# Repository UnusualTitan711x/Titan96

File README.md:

# Titan96  

**Titan96** is a compact 96% low-profile mechanical keyboard designed with sleek aesthetic. Powered by **KMK firmware** and built around the **Orpheus Pico microcontroller** by Hack Club.  

## Features  
- **96% Layout** – Compact yet functional, with all essential keys in a dense layout.  
- **Low-Profile Design** – Slimmer keys and case for a modern, ergonomic feel.  
- **KMK Firmware** – Highly customizable keymaps and macros using CircuitPython.  
- **Orpheus Pico MCU** – A powerful and open-source microcontroller by Hack Club.  
- **100 Keys** – Full numpad and navigation keys.  

## Parts
### CAD

### Schematic

### PCB

## Firmware & Software  
The Titan96 runs on **KMK**, a Python-based keyboard firmware for CircuitPython-compatible microcontrollers.  

### Setup Instructions  
1. **Flash CircuitPython** onto the Orpheus Pico.  
2. **Install KMK firmware** by copying the KMK files to the microcontroller.  
3. **Configure keymap** by editing `code.py` to match your layout.  
4. **Customize macros, layers, and RGB** (if supported) via KMK.  

For detailed KMK setup, refer to the [official KMK documentation](https://github.com/KMKfw/kmk_firmware).  

## Bill of Materials (BOM)  
| Part | Quantity | Price | Link | Notes |  
|------|----------|-------|------|-------|  
| Orpheus Pico MCU | 1 | N/A | N/A | Microcontroller by Hack Club |  
| Low-profile mechanical switches | 100 | $40.07 | [AliExpress](https://www.aliexpress.com/item/1005004620638633.html?spm=a2g0o.cart.0.0.422438daRMYwqx&mp=1&pdp_npi=5%40dis%21USD%21USD%2038.00%21USD%2034.20%21%21USD%2034.20%21%21%21%40211b65de17522704719968508eea63%2112000029862619758%21ct%21CM%216291529643%21%211%210) | Gateron Low-Profile |  
| Keycaps | 100 | $22.14 | [AliExpress](https://www.aliexpress.com/item/1005007074678857.html?spm=a2g0o.cart.0.0.422438daRMYwqx&mp=1&pdp_npi=5%40dis%21USD%21USD%2018.72%21USD%2014.98%21%21USD%2014.98%21%21%21%40211b65de17522704719968508eea63%2112000043563688519%21ct%21CM%216291529643%21%211%210) | MX stems |  
| PCB | 1 | N/A |  N/A | Custom Titan96 PCB |  
| Plate | 1 |  N/A | N/A |3D printed |  
| Case | 1 | N/A | N/A | 3D printed |  
| Diodes | 100 | $4.7 | [AliExpress](https://www.aliexpress.com/item/1005004333197874.html?spm=a2g0o.cart.0.0.422438daRMYwqx&mp=1&pdp_npi=5%40dis%21USD%21USD%200.33%21USD%200.31%21%21USD%200.31%21%21%21%40211b65de17522704719968508eea63%2112000028793174971%21ct%21CM%216291529643%21%211%210) | 1N4148 |  
| Stabilizers | 2u x 5, 6.5u x 1 | $15.58 | [AliExpress](https://www.aliexpress.com/item/1005005296240590.html?spm=a2g0o.cart.0.0.422438daRMYwqx&mp=1&pdp_npi=5%40dis%21USD%21USD%2011.59%21USD%2011.59%21%21USD%2011.59%21%21%21%40211b65de17522704719968508eea63%2112000032530884498%21ct%21CM%216291529643%21%211%210) | For larger keys (spacebar, Enter, etc.) |  
| OLED Screen 128 x 32 | 1 | $5.36 | [AliExpress](https://www.aliexpress.com/item/1005008670382155.html?spm=a2g0o.cart.0.0.422438daRMYwqx&mp=1&pdp_npi=5%40dis%21USD%21USD%201.63%21USD%201.14%21%21USD%201.14%21%21%21%40211b65de17522704719968508eea63%2112000046171658344%21ct%21CM%216291529643%21%211%210) | Screen |  
| M2 screws | 5 | $4.8 | [AliExpress](https://www.aliexpress.com/item/1005004533251852.html?spm=a2g0o.cart.0.0.286f38dacsLKbg&mp=1&pdp_npi=5%40dis%21USD%21USD%201.55%21USD%201.32%21%21USD%201.32%21%21%21%40211b618e17522580510792994e43dd%2112000029523312277%21ct%21CM%216291529643%21%211%210) | To screw the plate into the case |
| M2 threaded inserts | 5 | $5.87 | [AliExpress](https://www.aliexpress.com/item/1005003582355741.html?spm=a2g0o.cart.0.0.286f38dacsLKbg&mp=1&pdp_npi=5%40dis%21USD%21USD%201.69%21USD%200.52%21%21USD%200.52%21%21%21%40211b618e17522580510792994e43dd%2112000026370649721%21ct%21CM%216291529643%21%211%210) | To screw the plate into the case |
 
*NB: All these prices include shipping to Cameroon*

Total : $98.52
## License  
This project is open-source under the **MIT License**.  

## Extra Renders

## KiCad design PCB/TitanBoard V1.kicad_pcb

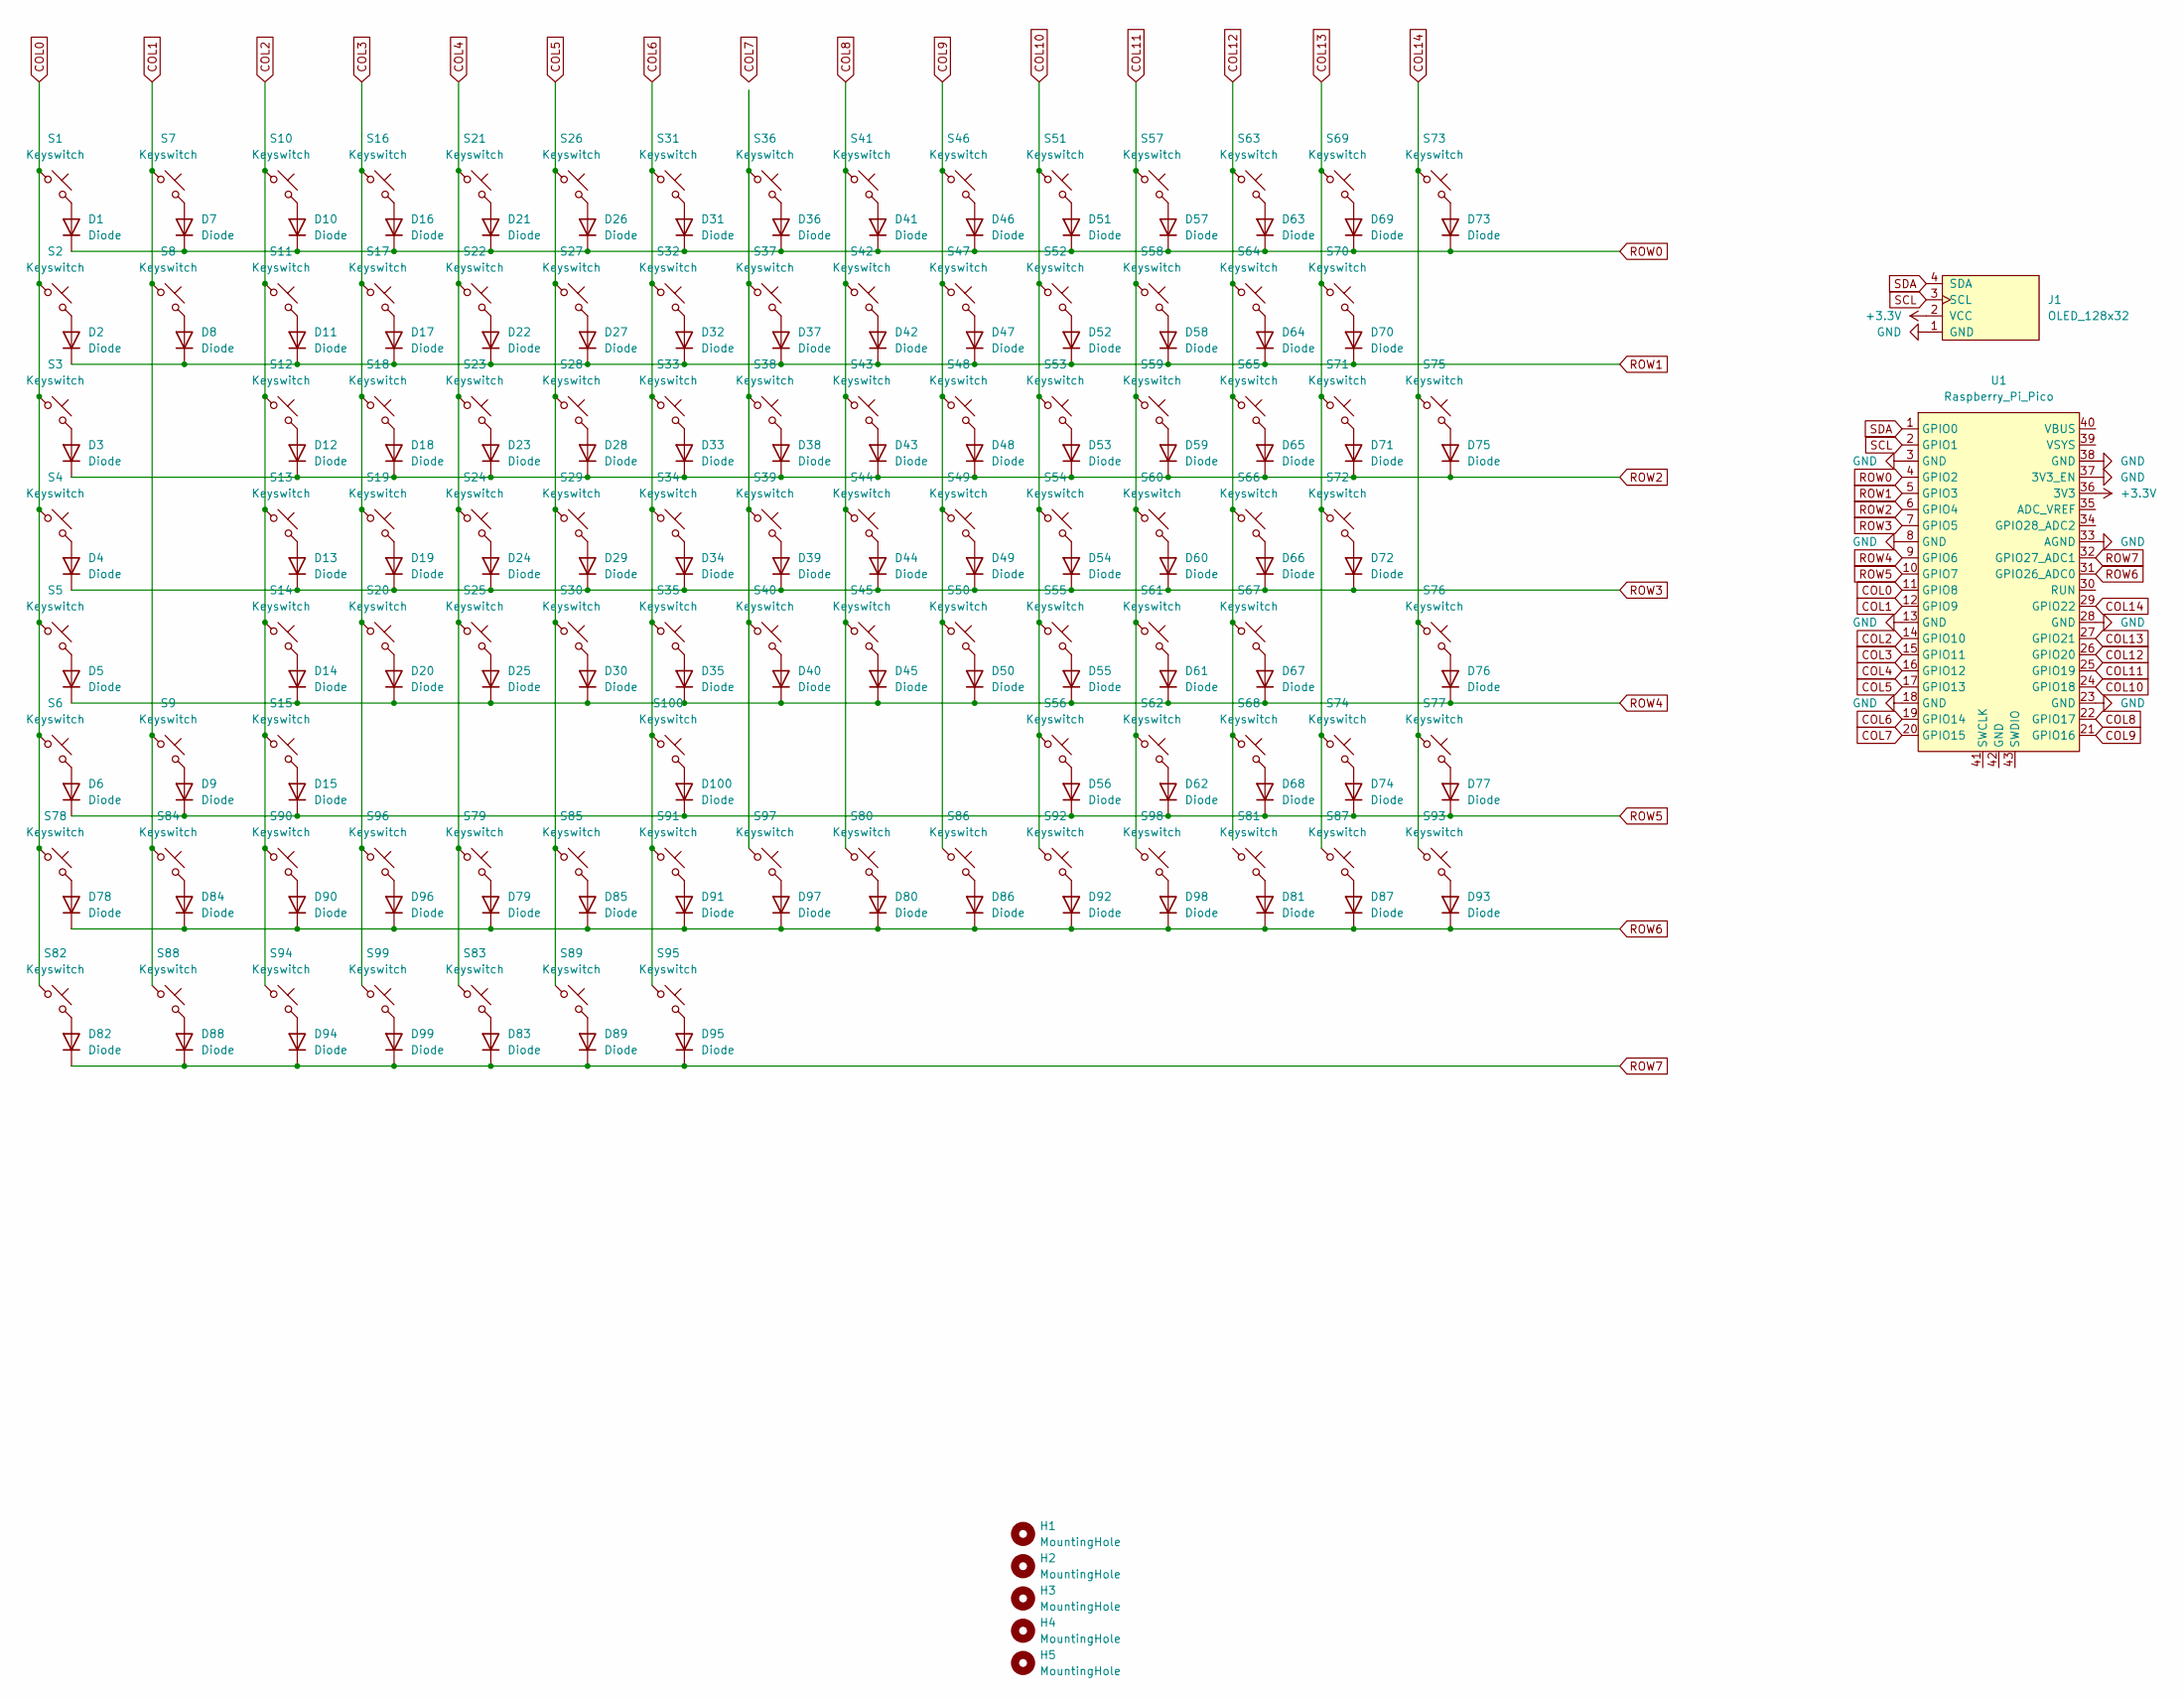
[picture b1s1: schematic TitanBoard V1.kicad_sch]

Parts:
D1, D2, D3, D4, D5, D6, D7, D8, D9, D10, D11, D12, D13, D14, D15, D16, D17, D18, D19, D20, D21, D22, D23, D24, D25, D26, D27, D28, D29, D30, D31, D32, D33, D34, D35, D36, D37, D38, D39, D40, D41, D42, D43, D44, D45, D46, D47, D48, D49, D50, D51, D52, D53, D54, D55, D56, D57, D58, D59, D60, D61, D62, D63, D64, D65, D66, D67, D68, D69, D70, D71, D72, D73, D74, D75, D76, D77, D78, D79, D80, D81, D82, D83, D84, D85, D86, D87, D88, D89, D90, D91, D92, D93, D94, D95, D96, D97, D98, D99, D100: Diode; Diode_DO-35
H1, H2, H3, H4, H5: MountingHole; MountingHole_2.2mm_M2
J1: OLED_128x32
S1, S2, S7, S8, S10, S11, S12, S13, S14, S16, S17, S18, S19, S20, S21, S22, S23, S24, S25, S26, S27, S28, S29, S30, S31, S32, S33, S34, S35, S36, S37, S38, S39, S40, S41, S42, S43, S44, S45, S46, S47, S48, S49, S50, S51, S52, S53, S54, S55, S56, S57, S58, S59, S60, S61, S62, S63, S64, S65, S66, S68, S69, S71, S73, S74, S76, S77, S78, S79, S80, S81, S82, S83, S84, S85, S86, S87, S88, S89, S90, S91, S92, S93, S94, S95, S96, S97: Keyswitch; Gateron-KS33-Solderable-1U
S3, S75: Keyswitch; Gateron-KS33-Solderable-1.5U
S4, S67: Keyswitch; Gateron-KS33-Solderable-1.75U
S5, S72: Keyswitch; Gateron-KS33-Solderable-2.25U
S6, S9, S15: Keyswitch; Gateron-KS33-Solderable-1.25U
S70, S98, S99: Keyswitch; Gateron-KS33-Solderable-2U
S100: Keyswitch; Gateron-KS33-Solderable-6.25U
U1: Raspberry_Pi_Pico

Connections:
+3.3V: J1.2 (VCC), U1.36 (3V3)
COL0: S1.1, S2.1, S3.1, S4.1, S5.1, S6.1, S78.1, S82.1, U1.11 (GPIO8)
COL1: S7.1, S8.1, S9.1, S84.1, S88.1, U1.12 (GPIO9)
COL2: S10.1, S11.1, S12.1, S13.1, S14.1, S15.1, S90.1, S94.1, U1.14 (GPIO10)
COL3: S16.1, S17.1, S18.1, S19.1, S20.1, S96.1, S99.1, U1.15 (GPIO11)
COL4: S21.1, S22.1, S23.1, S24.1, S25.1, S79.1, S83.1, U1.16 (GPIO12)
COL5: S26.1, S27.1, S28.1, S29.1, S30.1, S85.1, S89.1, U1.17 (GPIO13)
COL6: S31.1, S32.1, S33.1, S34.1, S35.1, S91.1, S95.1, S100.1, U1.19 (GPIO14)
COL7: U1.20 (GPIO15)
COL8: S41.1, S42.1, S43.1, S44.1, S45.1, S80.1, U1.22 (GPIO17)
COL9: S46.1, S47.1, S48.1, S49.1, S50.1, S86.1, U1.21 (GPIO16)
COL10: S51.1, S52.1, S53.1, S54.1, S55.1, S56.1, S92.1, U1.24 (GPIO18)
COL11: S57.1, S58.1, S59.1, S60.1, S61.1, S62.1, S98.1, U1.25 (GPIO19)
COL12: S63.1, S64.1, S65.1, S66.1, S67.1, S68.1, U1.26 (GPIO20)
COL13: S69.1, S70.1, S71.1, S72.1, S74.1, S87.1, U1.27 (GPIO21)
COL14: S73.1, S75.1, S76.1, S77.1, S93.1, U1.29 (GPIO22)
GND: J1.1 (GND), U1.3 (GND), U1.8 (GND), U1.13 (GND), U1.18 (GND), U1.23 (GND), U1.28 (GND), U1.33 (AGND), U1.37 (3V3_EN), U1.38 (GND)
unnamed: D1.2 (A), S1.2
unnamed: D2.2 (A), S2.2
unnamed: D3.2 (A), S3.2
unnamed: D4.2 (A), S4.2
unnamed: D5.2 (A), S5.2
unnamed: D6.2 (A), S6.2
unnamed: D7.2 (A), S7.2
unnamed: D8.2 (A), S8.2
unnamed: D9.2 (A), S9.2
unnamed: D10.2 (A), S10.2
unnamed: D11.2 (A), S11.2
unnamed: D12.2 (A), S12.2
unnamed: D13.2 (A), S13.2
unnamed: D14.2 (A), S14.2
unnamed: D15.2 (A), S15.2
unnamed: D16.2 (A), S16.2
unnamed: D17.2 (A), S17.2
unnamed: D18.2 (A), S18.2
unnamed: D19.2 (A), S19.2
unnamed: D20.2 (A), S20.2
unnamed: D21.2 (A), S21.2
unnamed: D22.2 (A), S22.2
unnamed: D23.2 (A), S23.2
unnamed: D24.2 (A), S24.2
unnamed: D25.2 (A), S25.2
unnamed: D26.2 (A), S26.2
unnamed: D27.2 (A), S27.2
unnamed: D28.2 (A), S28.2
unnamed: D29.2 (A), S29.2
unnamed: D30.2 (A), S30.2
unnamed: D31.2 (A), S31.2
unnamed: D32.2 (A), S32.2
unnamed: D33.2 (A), S33.2
unnamed: D34.2 (A), S34.2
unnamed: D35.2 (A), S35.2
unnamed: D36.2 (A), S36.2
unnamed: D37.2 (A), S37.2
unnamed: D38.2 (A), S38.2
unnamed: D39.2 (A), S39.2
unnamed: D40.2 (A), S40.2
unnamed: D41.2 (A), S41.2
unnamed: D42.2 (A), S42.2
unnamed: D43.2 (A), S43.2
unnamed: D44.2 (A), S44.2
unnamed: D45.2 (A), S45.2
unnamed: D46.2 (A), S46.2
unnamed: D47.2 (A), S47.2
unnamed: D48.2 (A), S48.2
unnamed: D49.2 (A), S49.2
unnamed: D50.2 (A), S50.2
unnamed: D51.2 (A), S51.2
unnamed: D52.2 (A), S52.2
unnamed: D53.2 (A), S53.2
unnamed: D54.2 (A), S54.2
unnamed: D55.2 (A), S55.2
unnamed: D56.2 (A), S56.2
unnamed: D57.2 (A), S57.2
unnamed: D58.2 (A), S58.2
unnamed: D59.2 (A), S59.2
unnamed: D60.2 (A), S60.2
unnamed: D61.2 (A), S61.2
unnamed: D62.2 (A), S62.2
unnamed: D63.2 (A), S63.2
unnamed: D64.2 (A), S64.2
unnamed: D65.2 (A), S65.2
unnamed: D66.2 (A), S66.2
unnamed: D67.2 (A), S67.2
unnamed: D68.2 (A), S68.2
unnamed: D69.2 (A), S69.2
unnamed: D70.2 (A), S70.2
unnamed: D71.2 (A), S71.2
unnamed: D72.2 (A), S72.2
unnamed: D73.2 (A), S73.2
unnamed: D74.2 (A), S74.2
unnamed: D75.2 (A), S75.2
unnamed: D76.2 (A), S76.2
unnamed: D77.2 (A), S77.2
unnamed: D78.2 (A), S78.2
unnamed: D79.2 (A), S79.2
unnamed: D80.2 (A), S80.2
unnamed: D81.2 (A), S81.2
unnamed: D82.2 (A), S82.2
unnamed: D83.2 (A), S83.2
unnamed: D84.2 (A), S84.2
unnamed: D85.2 (A), S85.2
unnamed: D86.2 (A), S86.2
unnamed: D87.2 (A), S87.2
unnamed: D88.2 (A), S88.2
unnamed: D89.2 (A), S89.2
unnamed: D90.2 (A), S90.2
unnamed: D91.2 (A), S91.2
unnamed: D92.2 (A), S92.2
unnamed: D93.2 (A), S93.2
unnamed: D94.2 (A), S94.2
unnamed: D95.2 (A), S95.2
unnamed: D96.2 (A), S96.2
unnamed: D97.2 (A), S97.2
unnamed: D98.2 (A), S98.2
unnamed: D99.2 (A), S99.2
unnamed: D100.2 (A), S100.2
unnamed: S36.1, S37.1, S38.1, S39.1, S40.1, S97.1
ROW0: D1.1 (K), D7.1 (K), D10.1 (K), D16.1 (K), D21.1 (K), D26.1 (K), D31.1 (K), D36.1 (K), D41.1 (K), D46.1 (K), D51.1 (K), D57.1 (K), D63.1 (K), D69.1 (K), D73.1 (K), U1.4 (GPIO2)
ROW1: D2.1 (K), D8.1 (K), D11.1 (K), D17.1 (K), D22.1 (K), D27.1 (K), D32.1 (K), D37.1 (K), D42.1 (K), D47.1 (K), D52.1 (K), D58.1 (K), D64.1 (K), D70.1 (K), U1.5 (GPIO3)
ROW2: D3.1 (K), D12.1 (K), D18.1 (K), D23.1 (K), D28.1 (K), D33.1 (K), D38.1 (K), D43.1 (K), D48.1 (K), D53.1 (K), D59.1 (K), D65.1 (K), D71.1 (K), D75.1 (K), U1.6 (GPIO4)
ROW3: D4.1 (K), D13.1 (K), D19.1 (K), D24.1 (K), D29.1 (K), D34.1 (K), D39.1 (K), D44.1 (K), D49.1 (K), D54.1 (K), D60.1 (K), D66.1 (K), D72.1 (K), U1.7 (GPIO5)
ROW4: D5.1 (K), D14.1 (K), D20.1 (K), D25.1 (K), D30.1 (K), D35.1 (K), D40.1 (K), D45.1 (K), D50.1 (K), D55.1 (K), D61.1 (K), D67.1 (K), D76.1 (K), U1.9 (GPIO6)
ROW5: D6.1 (K), D9.1 (K), D15.1 (K), D56.1 (K), D62.1 (K), D68.1 (K), D74.1 (K), D77.1 (K), D100.1 (K), U1.10 (GPIO7)
ROW6: D78.1 (K), D79.1 (K), D80.1 (K), D81.1 (K), D84.1 (K), D85.1 (K), D86.1 (K), D87.1 (K), D90.1 (K), D91.1 (K), D92.1 (K), D93.1 (K), D96.1 (K), D97.1 (K), D98.1 (K), U1.31 (GPIO26_ADC0)
ROW7: D82.1 (K), D83.1 (K), D88.1 (K), D89.1 (K), D94.1 (K), D95.1 (K), D99.1 (K), U1.32 (GPIO27_ADC1)
SCL: J1.3 (SCL), U1.2 (GPIO1)
SDA: J1.4 (SDA), U1.1 (GPIO0)

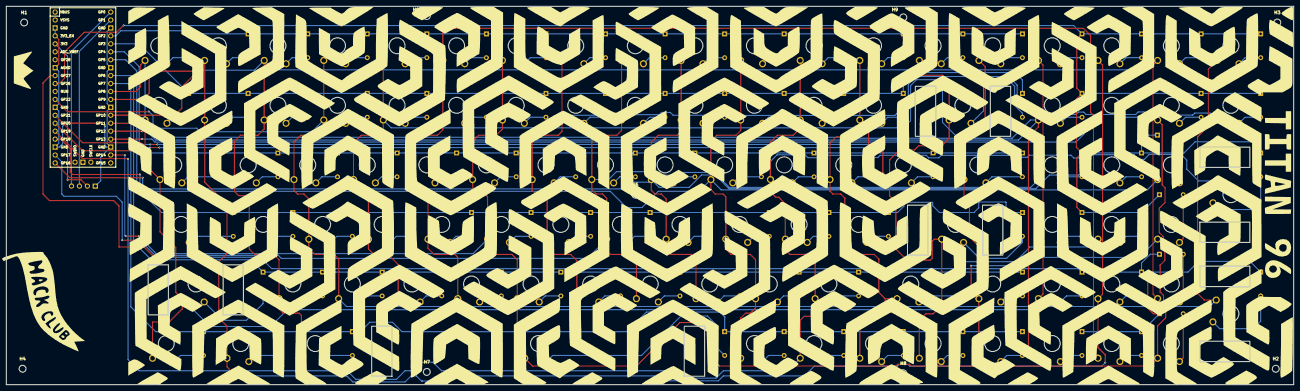
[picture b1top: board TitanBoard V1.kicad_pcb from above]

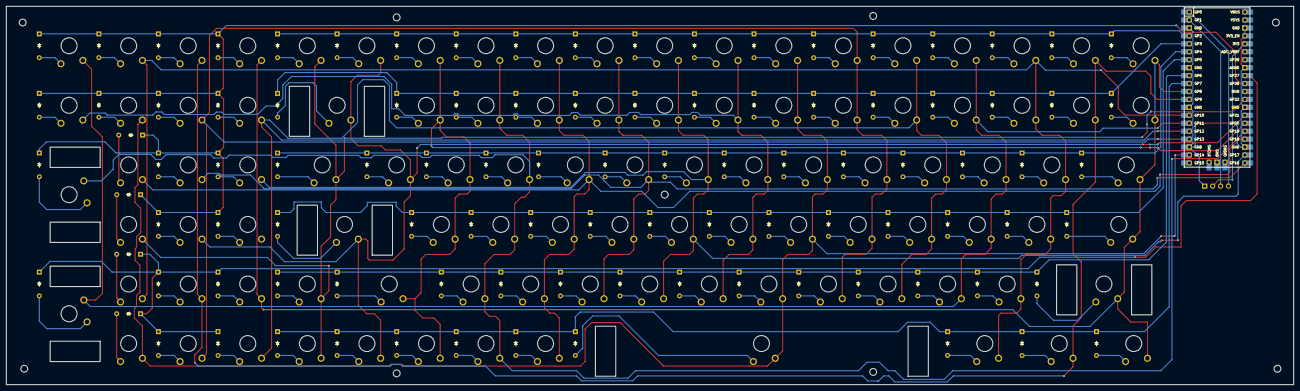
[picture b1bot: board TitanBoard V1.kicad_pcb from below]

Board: 2 copper layers, 411.8 x 121.0 mm, 211 parts (101 on the bottom side), 127 nets.

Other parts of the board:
H6, H7, H8, H9: MountingHole; MountingHole_2.2mm_M2

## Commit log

2025-04-15 added images
2025-04-15 added PCB stuff
2025-04-15 added case parts
2025-07-06 images and README update
2025-07-07 updated footprints
    made space for the plate mounted stabilizers
2025-07-11 updated CAD
